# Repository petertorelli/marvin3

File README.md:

# Introduction

## Part 1: Motor Controller

See the readme in [readme in the mc folder](https://github.com/petertorelli/marvin3/blob/main/mc/README.md) the motor controller.

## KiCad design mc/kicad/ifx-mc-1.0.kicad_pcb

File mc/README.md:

# Introduction

This is a brushed-DC, PID controlled, motor-controller designed to work with [GoBilda Yellowjack motors](https://www.gobilda.com/yellow-jacket-planetary-gear-motors). GoBilda makes a controller, but it doesn't use the decoder circuit. For me, this is part of a larger project and I need to know if wheels are stalled so that the MC can provide more current.

Output is 24 KHz PWM wave from zero to 95% duty cycle. The input is a standard servo controller 500~1500 ms at 50 Hz. It requires 12 VDC input, and supplies 5 V to the controller, motor decoder, and servo (which usually doesn't need it).

The PID is tuned to avoid overshoot spikes at a step function input, but I haven't tested the settings with all six motors running. Probably later this summer.

It uses an Infineon PSoC4 MCU, Infineon 140W NFETS, and Infineon IR2184 half-bridge drivers (notice the trend?). The motor stall current is 9A, and I wanted to makes sure the board could deliver that. (The ever-popular LM298 only delivers 2A.)

The schematic was drawn in KiCad and hand routed so that the high-current path has priority. I could have compacted it more, but with only two layers I had to make sure no MCU traces crossed the high-current return path on the bottom layer. So I put the MCU and its logic on the other side of the board, thus the XT30 power supply jumper RIGHT IN THE MIDDLE OF THE LAYOUT. I also used double-weight copper (0.2 oz) so that if it does stall at 9 A there's plenty of headroom.

I'm pleased with the progression from layout, to 3D rendering (I put way too much work into finding 3D models), and the actual board. Here is composite:

# To Do

1. The gate resistors are rated for 1/10th of a Watt, so I'm a little concerned they are gonna go \*poof\* at some point. I realize once the gate charges up there's miniscule voltage drop, but even the width of the peaks (shown below) should be out of spec, and nothing is even getting warm. So I'm probably misunderstand the electrical characteristics. (If you have any ideas, drop me a comment.)

3. I tried increasing the gate resistors to 100 Ohms and the slopes got worse, but the supply current increased significanlty. I wasn't expecting it to be so sensitive. I tried running without resistors and cooked several IR2184s (I know, the schematic indicates a resistor, just wanted to try).

33 Ohm slope vs 100 Ohm slope = 52 to 390 µs difference. Even if I moved the cursors to the 20%/80% slope points it still much more than expected.

4. I didn't need a fast-shutoff diode because 24 KHz is slow enough and I didn't want to cramp the layout, and it didn't make much difference. Here are with (left) and without (right):

6. The PID is set to 50 ms updates, and with 4x from the quadrature decoder I get 2400 pulses per second at full speed, or 120 per 50 ms. Seems to be working ok.

Here is the step function response and follow-response charts:

7. 48 MHz is probably a bit overpowered, as the main loop takes 6.3 µs when not updating the pid, and 9.3 µs when updating (reading the QUADDEC and a `printf`). Since this  outpaces the update speed of the PID at 50 ms I could have used an even smaller & slower version of the PSoC4 if they had enough PWMs. Note that a `while(1)` loop with just a GPIO toggle takes 340 ns. Turns out there's now a 12V version of PSOC4 so I could also ditch the linear regulator if there's a package match. (Should probably use an OPTIREG regulator so I can be 100% Infineon.)

8. I built it to use standard servo PWM signaling since the PWM counter doesn't need any CPU cycles, but since I also supplied a UART on the board for debug/telemetry, I could also just send exact values instead of having to decode a PWM.

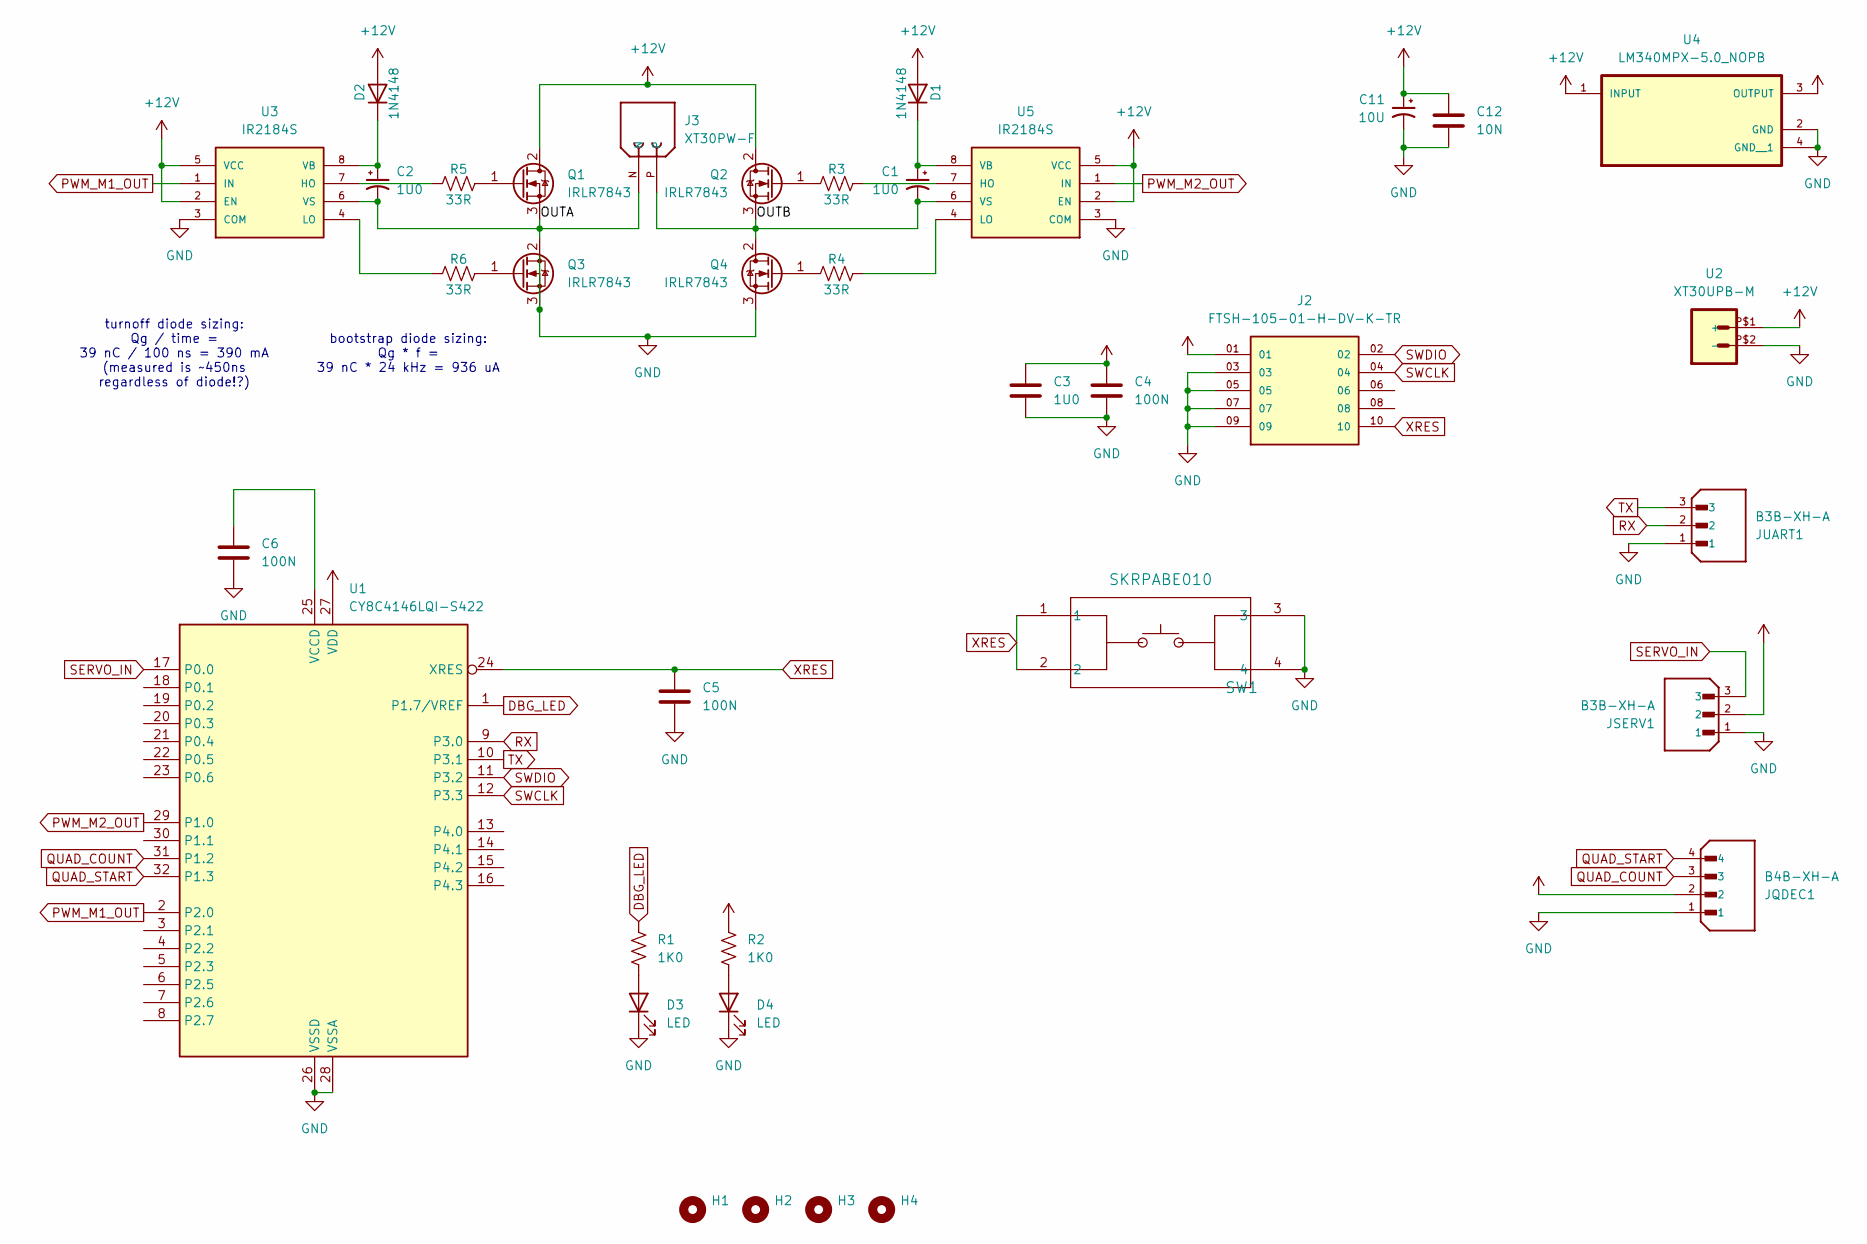
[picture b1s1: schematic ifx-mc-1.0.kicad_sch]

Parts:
C1, C2: 1U0; C_0603_1608Metric
C3: 1U0; C_0805_2012Metric
C4, C5, C6: 100N; C_0603_1608Metric
C11: 10U; CAP_865230340001
C12: 10N; C_0805_2012Metric
D1, D2: 1N4148; D_0603_1608Metric
D3, D4: LED; LED_0603_1608Metric_Pad1.05x0.95mm_HandSolder
H1, H2, H3, H4: MountingHole; MountingHole_3.2mm_M3_DIN965
J2: FTSH-105-01-H-DV-K-TR; SAMTEC_FTSH-105-01-H-DV-K-TR; PARTREV R
J3: XT30PW-F; AMASS_XT30PW-F; PARTREV 1.2
JQDEC1: B4B-XH-A; JST_B4B-XH-A; PARTREV 7/4/21
JSERV1: B3B-XH-A; JST_B3B-XH-A; PARTREV 7/4/21
JUART1: B3B-XH-A; JST_B3B-XH-A; PARTREV 7/4/21
Q1, Q2, Q3, Q4: IRLR7843; TO-252-2
R1, R2: 1K0; R_0603_1608Metric_Pad0.98x0.95mm_HandSolder
R3, R4, R5, R6: 33R; R_0603_1608Metric
SW1: SKRPABE010; SW4_SKRPABE010_ALPS
U1: CY8C4146LQI-S422; VQFN-32-1EP_5x5mm_P0.5mm_EP3.5x3.5mm
U2: XT30UPB-M
U3, U5: IR2184S; SOIC8_INF; MPN IR2184S
U4: LM340MPX-5.0_NOPB; SOT230P700X180-4N

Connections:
+12V: C11.1, C12.1, D1.2 (A), D2.2 (A), Q1.2 (D), Q2.2 (D), U2.P$1 (+), U3.2 (EN), U3.5 (VCC), U4.1 (INPUT), U5.2 (EN), U5.5 (VCC)
/OUTA: C2.2, J3.N, Q1.3 (S), Q3.2 (D), U3.6 (VS)
/OUTB: C1.2, J3.P, Q2.3 (S), Q4.2 (D), U5.6 (VS)
DBG_LED: R1.1, U1.1 (P1.7/VREF)
GND: C3.2, C4.2, C5.2, C6.2, C11.2, C12.2, D3.1 (K), D4.1 (K), J2.03, J2.05, J2.07, J2.09, JQDEC1.1, JSERV1.1, JUART1.1, Q3.3 (S), Q4.3 (S), SW1.3, SW1.4, U1.26 (VSSD), U1.28 (VSSA), U2.P$2 (-), U3.3 (COM), U4.2 (GND), U4.4 (GND__1), U5.3 (COM)
unnamed: C1.1, D1.1 (K), U5.8 (VB)
unnamed: C2.1, D2.1 (K), U3.8 (VB)
unnamed: D3.2 (A), R1.2
unnamed: D4.2 (A), R2.2
unnamed: Q1.1 (G), R5.1
unnamed: Q2.1 (G), R3.2
unnamed: Q3.1 (G), R6.1
unnamed: Q4.1 (G), R4.2
unnamed: C6.1, U1.25 (VCCD)
unnamed: R5.2, U3.7 (HO)
unnamed: R6.2, U3.4 (LO)
unnamed: R3.1, U5.7 (HO)
unnamed: R4.1, U5.4 (LO)
PWM_M1_OUT: U1.2 (P2.0), U3.1 (IN)
PWM_M2_OUT: U1.29 (P1.0), U5.1 (IN)
QUAD_COUNT: JQDEC1.3, U1.31 (P1.2)
QUAD_START: JQDEC1.4, U1.32 (P1.3)
RX: JUART1.2, U1.9 (P3.0)
SERVO_IN: JSERV1.3, U1.17 (P0.0)
SWCLK: J2.04, U1.12 (P3.3)
SWDIO: J2.02, U1.11 (P3.2)
TX: JUART1.3, U1.10 (P3.1)
VCC: C3.1, C4.1, J2.01, JQDEC1.2, JSERV1.2, R2.1, U1.27 (VDD), U4.3 (OUTPUT)
XRES: C5.1, J2.10, SW1.1, SW1.2, U1.24 (XRES)

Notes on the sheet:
bootstrap diode sizing: Qg * f = 39 nC * 24 kHz = 936 uA
turnoff diode sizing: Qg / time = 39 nC / 100 ns = 390 mA (measured is ~450ns regardless of diode!?)

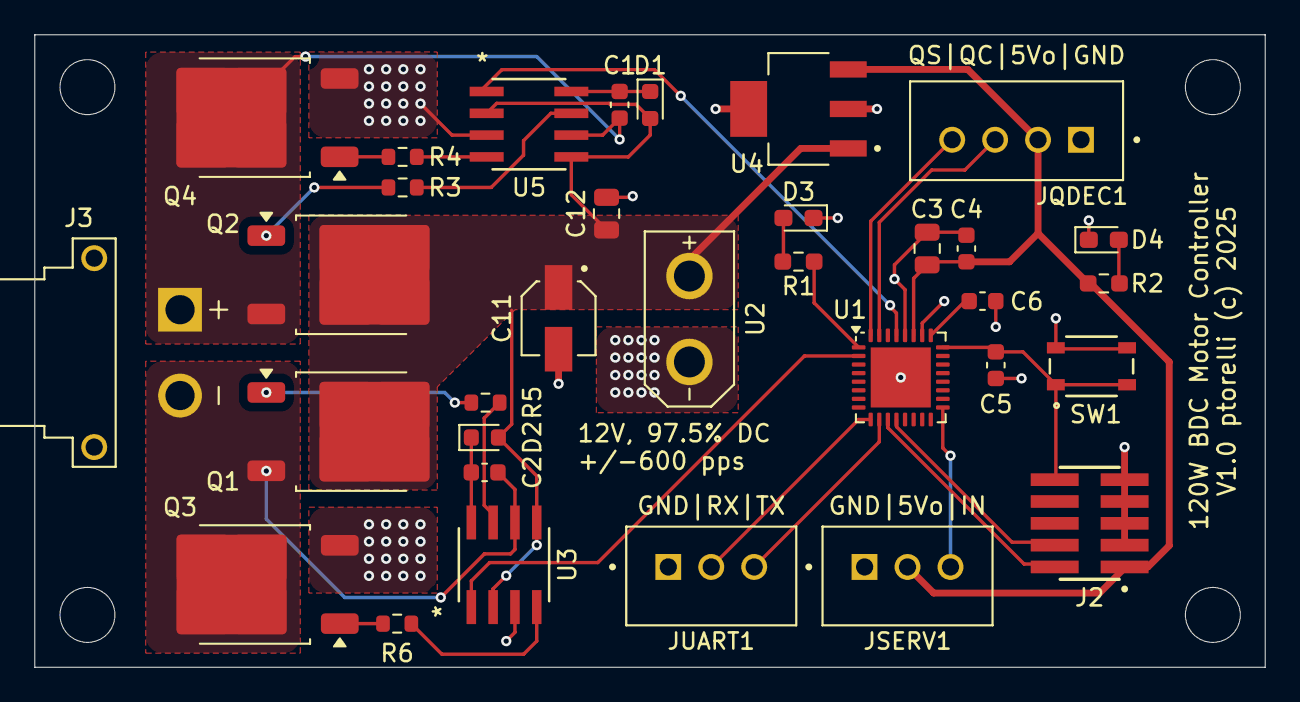
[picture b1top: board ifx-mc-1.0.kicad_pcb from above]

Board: 2 copper layers, 71.6 x 36.8 mm, 37 parts (0 on the bottom side), 29 nets.

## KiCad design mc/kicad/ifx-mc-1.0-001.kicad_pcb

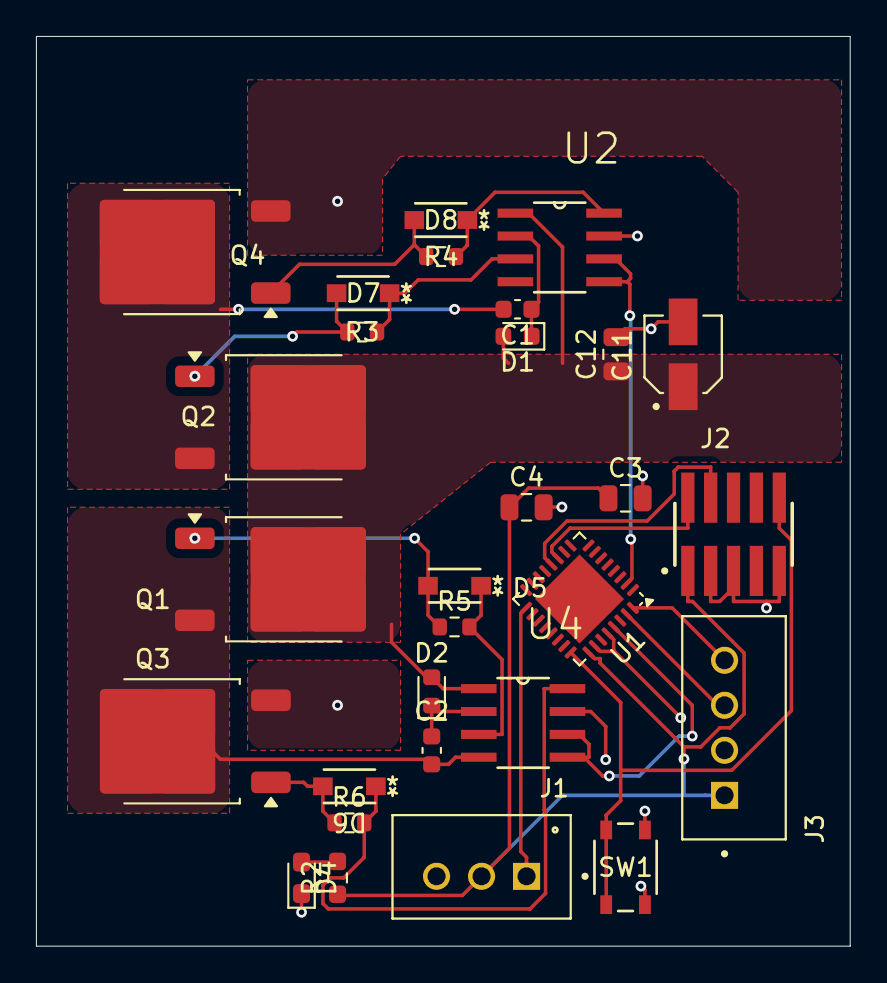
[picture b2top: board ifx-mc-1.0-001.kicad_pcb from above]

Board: 2 copper layers, 45.2 x 50.5 mm, 29 parts (0 on the bottom side), 24 nets.

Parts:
C1, C2: 1U0; C_0603_1608Metric
C3, C4: C; C_0805_2012Metric
C11: 10U; CAP_865230340001
C12: 10N; C_0805_2012Metric
D1, D2: 1N4148; D_0603_1608Metric
D4: LED; LED_0603_1608Metric_Pad1.05x0.95mm_HandSolder
D5, D6, D7, D8: RF071MM2S; DIO_RB051MM_ROM
J1: B3B-XH-A; JST_B3B-XH-A
J2: FTSH-105-01-H-DV-K-TR; SAMTEC_FTSH-105-01-H-DV-K-TR
J3: B4B-XH-A; JST_B4B-XH-A
Q1, Q2, Q3, Q4: IRLR7843; TO-252-2
R2: R_US; R_0603_1608Metric_Pad0.98x0.95mm_HandSolder
R3, R4, R5, R6: 33; R_0603_1608Metric
SW1: SKRPABE010; SW4_SKRPABE010_ALPS
U1: CY8C4146LQI-S422; VQFN-32-1EP_5x5mm_P0.5mm_EP3.5x3.5mm
U2, U4: IR2011; SOIC127P600X175-8N

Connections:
+12V: C11.1, C12.1, D1.2 (A), D2.2 (A), Q1.2 (D), Q2.2 (D), U2.1 (VCC), U4.1 (VCC)
/OUTA: C2.2, Q1.3 (S), Q3.2 (D), U4.4 (VS)
/OUTB: C1.2, Q2.3 (S), Q4.2 (D), U2.4 (VS)
GND: C3.2, C4.2, C11.2, C12.2, D4.1 (K), J1.3, J2.03, J2.05, J2.09, J3.2, Q3.3 (S), Q4.3 (S), SW1.3, SW1.4, U1.26 (VSSD), U1.28 (VSSA), U2.7 (COM), U4.7 (COM)
unnamed: C1.1, D1.1 (K), U2.2 (VB)
unnamed: C2.1, D2.1 (K), U4.2 (VB)
unnamed: D4.2 (A), R2.2
unnamed: D5.2 (A), Q1.1 (G), R5.1
unnamed: D5.1 (K), R5.2, U4.3 (HO)
unnamed: D6.2 (A), Q3.1 (G), R6.1
unnamed: D6.1 (K), R6.2, U4.8 (LO)
unnamed: D7.2 (A), Q2.1 (G), R3.2
unnamed: D7.1 (K), R3.1, U2.3 (HO)
unnamed: D8.2 (A), Q4.1 (G), R4.2
unnamed: D8.1 (K), R4.1, U2.8 (LO)
PWM_M1_OUT: U1.29 (P1.0), U4.5 (HIN), U4.6 (LIN)
PWM_M2_OUT: U1.2 (P2.0), U2.5 (HIN), U2.6 (LIN)
QUAD_COUNT: J3.3, U1.31 (P1.2)
QUAD_START: J3.4, U1.32 (P1.3)
SERVO_IN: J1.1, U1.17 (P0.0)
SWCLK: J2.04, U1.12 (P3.3)
SWDIO: J2.02, U1.11 (P3.2)
VCC: C3.1, C4.1, J1.2, J2.01, J3.1, R2.1, U1.25 (VCCD), U1.27 (VDD)
XRES: J2.10, SW1.1, SW1.2, U1.24 (XRES)

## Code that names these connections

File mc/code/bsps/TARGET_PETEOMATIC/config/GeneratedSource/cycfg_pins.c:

/*******************************************************************************
 * File Name: cycfg_pins.c
 *
 * Description:
 * Pin configuration
 * This file was automatically generated and should not be modified.
 * Configurator Backend 3.40.0
 * device-db 4.20.0.7450
 * mtb-pdl-cat2 2.14.0.14518
 *
 *******************************************************************************
 * Copyright 2025 Cypress Semiconductor Corporation (an Infineon company) or
 * an affiliate of Cypress Semiconductor Corporation.
 * SPDX-License-Identifier: Apache-2.0
 *
 * Licensed under the Apache License, Version 2.0 (the "License");
 * you may not use this file except in compliance with the License.
 * You may obtain a copy of the License at
 *
 *     http://www.apache.org/licenses/LICENSE-2.0
 *
 * Unless required by applicable law or agreed to in writing, software
 * distributed under the License is distributed on an "AS IS" BASIS,
 * WITHOUT WARRANTIES OR CONDITIONS OF ANY KIND, either express or implied.
 * See the License for the specific language governing permissions and
 * limitations under the License.
 ******************************************************************************/

#include "cycfg_pins.h"

const cy_stc_gpio_pin_config_t SERVO_IN_config =
{
    .outVal = 1,
    .driveMode = CY_GPIO_DM_HIGHZ,
    .hsiom = SERVO_IN_HSIOM,
    .intEdge = CY_GPIO_INTR_DISABLE,
    .vtrip = CY_GPIO_VTRIP_CMOS,
    .slewRate = CY_GPIO_SLEW_FAST,
};

#if defined (CY_USING_HAL)
const cyhal_resource_inst_t SERVO_IN_obj =
{
    .type = CYHAL_RSC_GPIO,
    .block_num = SERVO_IN_PORT_NUM,
    .channel_num = SERVO_IN_PIN,
};
#endif /* defined (CY_USING_HAL) */

const cy_stc_gpio_pin_config_t PWM_LHS_OUT_config =
{
    .outVal = 1,
    .driveMode = CY_GPIO_DM_STRONG_IN_OFF,
    .hsiom = PWM_LHS_OUT_HSIOM,
    .intEdge = CY_GPIO_INTR_DISABLE,
    .vtrip = CY_GPIO_VTRIP_CMOS,
    .slewRate = CY_GPIO_SLEW_FAST,
};

#if defined (CY_USING_HAL)
const cyhal_resource_inst_t PWM_LHS_OUT_obj =
{
    .type = CYHAL_RSC_GPIO,
    .block_num = PWM_LHS_OUT_PORT_NUM,
    .channel_num = PWM_LHS_OUT_PIN,
};
#endif /* defined (CY_USING_HAL) */

const cy_stc_gpio_pin_config_t QUAD_COUNT_config =
{
    .outVal = 1,
    .driveMode = CY_GPIO_DM_HIGHZ,
    .hsiom = QUAD_COUNT_HSIOM,
    .intEdge = CY_GPIO_INTR_DISABLE,
    .vtrip = CY_GPIO_VTRIP_CMOS,
    .slewRate = CY_GPIO_SLEW_FAST,
};

#if defined (CY_USING_HAL)
const cyhal_resource_inst_t QUAD_COUNT_obj =
{
    .type = CYHAL_RSC_GPIO,
    .block_num = QUAD_COUNT_PORT_NUM,
    .channel_num = QUAD_COUNT_PIN,
};
#endif /* defined (CY_USING_HAL) */

const cy_stc_gpio_pin_config_t QUAD_START_config =
{
    .outVal = 1,
    .driveMode = CY_GPIO_DM_HIGHZ,
    .hsiom = QUAD_START_HSIOM,
    .intEdge = CY_GPIO_INTR_DISABLE,
    .vtrip = CY_GPIO_VTRIP_CMOS,
    .slewRate = CY_GPIO_SLEW_FAST,
};

#if defined (CY_USING_HAL)
const cyhal_resource_inst_t QUAD_START_obj =
{
    .type = CYHAL_RSC_GPIO,
    .block_num = QUAD_START_PORT_NUM,
    .channel_num = QUAD_START_PIN,
};
#endif /* defined (CY_USING_HAL) */

const cy_stc_gpio_pin_config_t DBG_LED_config =
{
    .outVal = 1,
    .driveMode = CY_GPIO_DM_STRONG_IN_OFF,
    .hsiom = DBG_LED_HSIOM,
    .intEdge = CY_GPIO_INTR_DISABLE,
    .vtrip = CY_GPIO_VTRIP_CMOS,
    .slewRate = CY_GPIO_SLEW_FAST,
};

#if defined (CY_USING_HAL)
const cyhal_resource_inst_t DBG_LED_obj =
{
    .type = CYHAL_RSC_GPIO,
    .block_num = DBG_LED_PORT_NUM,
    .channel_num = DBG_LED_PIN,
};
#endif /* defined (CY_USING_HAL) */

const cy_stc_gpio_pin_config_t PWM_RHS_OUT_config =
{
    .outVal = 1,
    .driveMode = CY_GPIO_DM_STRONG_IN_OFF,
    .hsiom = PWM_RHS_OUT_HSIOM,
    .intEdge = CY_GPIO_INTR_DISABLE,
    .vtrip = CY_GPIO_VTRIP_CMOS,
    .slewRate = CY_GPIO_SLEW_FAST,
};

#if defined (CY_USING_HAL)
const cyhal_resource_inst_t PWM_RHS_OUT_obj =
{
    .type = CYHAL_RSC_GPIO,
    .block_num = PWM_RHS_OUT_PORT_NUM,
    .channel_num = PWM_RHS_OUT_PIN,
};
#endif /* defined (CY_USING_HAL) */

const cy_stc_gpio_pin_config_t ADC_IN_config =
{
    .outVal = 1,
    .driveMode = CY_GPIO_DM_ANALOG,
    .hsiom = ADC_IN_HSIOM,
    .intEdge = CY_GPIO_INTR_DISABLE,
    .vtrip = CY_GPIO_VTRIP_CMOS,
    .slewRate = CY_GPIO_SLEW_FAST,
};

#if defined (CY_USING_HAL)
const cyhal_resource_inst_t ADC_IN_obj =
{
    .type = CYHAL_RSC_GPIO,
    .block_num = ADC_IN_PORT_NUM,
    .channel_num = ADC_IN_PIN,
};
#endif /* defined (CY_USING_HAL) */

const cy_stc_gpio_pin_config_t UART_RX_config =
{
    .outVal = 1,
    .driveMode = CY_GPIO_DM_HIGHZ,
    .hsiom = UART_RX_HSIOM,
    .intEdge = CY_GPIO_INTR_DISABLE,
    .vtrip = CY_GPIO_VTRIP_CMOS,
    .slewRate = CY_GPIO_SLEW_FAST,
};

#if defined (CY_USING_HAL)
const cyhal_resource_inst_t UART_RX_obj =
{
    .type = CYHAL_RSC_GPIO,
    .block_num = UART_RX_PORT_NUM,
    .channel_num = UART_RX_PIN,
};
#endif /* defined (CY_USING_HAL) */

const cy_stc_gpio_pin_config_t UART_TX_config =
{
    .outVal = 1,
    .driveMode = CY_GPIO_DM_STRONG_IN_OFF,
    .hsiom = UART_TX_HSIOM,
    .intEdge = CY_GPIO_INTR_DISABLE,
    .vtrip = CY_GPIO_VTRIP_CMOS,
    .slewRate = CY_GPIO_SLEW_FAST,
};

#if defined (CY_USING_HAL)
const cyhal_resource_inst_t UART_TX_obj =
{
    .type = CYHAL_RSC_GPIO,
    .block_num = UART_TX_PORT_NUM,
    .channel_num = UART_TX_PIN,
};
#endif /* defined (CY_USING_HAL) */

const cy_stc_gpio_pin_config_t SWDIO_config =
{
    .outVal = 1,
    .driveMode = CY_GPIO_DM_STRONG,
    .hsiom = SWDIO_HSIOM,
    .intEdge = CY_GPIO_INTR_DISABLE,
    .vtrip = CY_GPIO_VTRIP_CMOS,
    .slewRate = CY_GPIO_SLEW_FAST,
};

#if defined (CY_USING_HAL)
const cyhal_resource_inst_t SWDIO_obj =
{
    .type = CYHAL_RSC_GPIO,
    .block_num = SWDIO_PORT_NUM,
    .channel_num = SWDIO_PIN,
};
#endif /* defined (CY_USING_HAL) */

const cy_stc_gpio_pin_config_t SWCLK_config =
{
    .outVal = 1,
    .driveMode = CY_GPIO_DM_STRONG,
    .hsiom = SWCLK_HSIOM,
    .intEdge = CY_GPIO_INTR_DISABLE,
    .vtrip = CY_GPIO_VTRIP_CMOS,
    .slewRate = CY_GPIO_SLEW_FAST,
};

#if defined (CY_USING_HAL)
const cyhal_resource_inst_t SWCLK_obj =
{
    .type = CYHAL_RSC_GPIO,
    .block_num = SWCLK_PORT_NUM,
    .channel_num = SWCLK_PIN,
};
#endif /* defined (CY_USING_HAL) */

void init_cycfg_pins(void)
{
    Cy_GPIO_Pin_Init(SERVO_IN_PORT, SERVO_IN_PIN, &SERVO_IN_config);
    Cy_GPIO_Pin_Init(PWM_LHS_OUT_PORT, PWM_LHS_OUT_PIN, &PWM_LHS_OUT_config);
    Cy_GPIO_Pin_Init(QUAD_COUNT_PORT, QUAD_COUNT_PIN, &QUAD_COUNT_config);
    Cy_GPIO_Pin_Init(QUAD_START_PORT, QUAD_START_PIN, &QUAD_START_config);
    Cy_GPIO_Pin_Init(DBG_LED_PORT, DBG_LED_PIN, &DBG_LED_config);
    Cy_GPIO_Pin_Init(PWM_RHS_OUT_PORT, PWM_RHS_OUT_PIN, &PWM_RHS_OUT_config);
    Cy_GPIO_Pin_Init(ADC_IN_PORT, ADC_IN_PIN, &ADC_IN_config);
    Cy_GPIO_Pin_Init(UART_RX_PORT, UART_RX_PIN, &UART_RX_config);
    Cy_GPIO_Pin_Init(UART_TX_PORT, UART_TX_PIN, &UART_TX_config);
    Cy_GPIO_Pin_Init(SWDIO_PORT, SWDIO_PIN, &SWDIO_config);
    Cy_GPIO_Pin_Init(SWCLK_PORT, SWCLK_PIN, &SWCLK_config);
}
void reserve_cycfg_pins(void)
{
#if defined (CY_USING_HAL)
    cyhal_hwmgr_reserve(&SERVO_IN_obj);
    cyhal_hwmgr_reserve(&PWM_LHS_OUT_obj);
    cyhal_hwmgr_reserve(&QUAD_COUNT_obj);
    cyhal_hwmgr_reserve(&QUAD_START_obj);
    cyhal_hwmgr_reserve(&DBG_LED_obj);
    cyhal_hwmgr_reserve(&PWM_RHS_OUT_obj);
    cyhal_hwmgr_reserve(&ADC_IN_obj);
    cyhal_hwmgr_reserve(&UART_RX_obj);
    cyhal_hwmgr_reserve(&UART_TX_obj);
    cyhal_hwmgr_reserve(&SWDIO_obj);
    cyhal_hwmgr_reserve(&SWCLK_obj);
#endif /* defined (CY_USING_HAL) */
}

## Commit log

2025-03-07 Cleanup
2025-03-15 Some production tweaks
2025-03-15 Annoted wiring issue on JQDEC1
2025-03-15 Cleanup.
2025-03-15 README for MC
2025-03-15 new images
2025-03-16 new image

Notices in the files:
mc/kicad/ifx-mc-1.0.kicad_pcb:
V1.0 ptorelli (c) 2025
